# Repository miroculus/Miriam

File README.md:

Miriam
========

**🆕📻⚠️ IMPORTANT: A more updated repository which fixes several critical bugs is at https://github.com/strawlab/Miriam .**

Copyright Miroculus Inc.2016
Based on original work from Arduino (Sweden)

This documentation describes Open Hardware and is licensed under the CERN OHL v. 1.2.

Licensed under CERN OHL v.1.2

You may redistribute and modify this documentation under the terms of the [CERN OHL v.1.2.](http://ohwr.org/cernohl). This documentation is distributed WITHOUT ANY EXPRESS OR IMPLIED WARRANTY, INCLUDING OF MERCHANTABILITY, SATISFACTORY QUALITY AND FITNESS FOR A PARTICULAR PURPOSE. Please see the CERN OHL v.1.2 for applicable conditions

## Introduction

Miriam is an open-source instrument for isothermal amplification reactions. The assays Miriam was designed to execute are based on LAMP and Elisa protocols. Miriam is controlled with [Arduino](http://www.arduino.cc/) Mega and the production costs per instrument are blow 200USD.

The detection optics have been designed for [calcein dye](http://loopamp.eiken.co.jp/e/products/fluore/index.html). The selected LED is an angle SMD led with peak wavelength 461nm. The photodiode is an RGB photodiode most sensitive to green light. The optics also include an emission filter utilized in theatrical lighting.  The development and selection of components is further described in a [Master's thesis](http://lutpub.lut.fi/handle/10024/159386) done from miriam. 

In the performance testing of Miriam, the detection limit for DNA using LAMP as amplification platform has been 2amol in 10ul of sample (figure 1).

**Figure 1.** LAMP reaction with 2amol DNA input, fluorescence measured every 2 minutes (y, Normalized signal and x, cycle (2 min).

For more information, you can contact us by completing the form [here](https://miroculus.com/#contact). You can also follow Miroculus on [twitter](https://twitter.com/miroculus) or like us on [facebook](https://www.facebook.com/miroculus).

To report a *bug* in the software or to request *a simple enhancement* go to the [issues](http://github.com/miroculus/Miriam/issues) section

If you're interested in modifying or extending the Miriam platform, we strongly suggest you to send us an email discussing your ideas. That way you can coordinate with our team and others, giving your work a higher chance of being integrated into the official release.

## Design

The optics of Miriam are designed to support calcein dye. Calcein emission and excitation spectra are represented in Figure 2.

**Figure 2.** Calcein normalized emission and excitation spectra.

The optical filter for blocking the excitation light has been purchased from a theatrical supply store and has the transmission spectra represented in Figure 3.

**Figure 3.** Emission filter transmission specter.

The middle heating board and the LED and PD arrangements have been designed to support 96-well plates with the following dimensions (figure 4).

**Figure 4.** 96-well plate dimensions supported by Miriam

To control the heating of Miriam there are two heater PCBs. They have been designed so that in the middle is a 10 kohm SMD thermistor and the heat is generated by current flowing through the copper traces. These traces have been designed to be so long and narrow that they create an internal resistance of few ohms. The traces are closer to each other in the edges because heat is measured from the middle and the edges of the PCB boards meet ambient air and they need to produce more heat. (Figure 5.)

**Figure 5.** Heating plates, heat is generated by trace resistance. Right: The middle heater creating the temperature required for amplification (58-68 degrees C). Left: The top heater keeping vapor from condensing to the lid, kept at 80 degrees C. 

The detection of fluorescence is done with 96 LEDs and 96 photodiodes creating LED and photodiode PCBs. The LED peak wavelength is 470 nm and photodiode is a green RGB photodiode. The measured voltage is amplified with an operational amplifier to 0-5 V that is then converted by Arduino’s 8-bit ADC to be a numerical value. (figure 6.)

**Figure 6.** LED (left) and photodiode (right) PCBs.

All of these boards are controlled by a shield that is directly mounted to the Arduino mega board (figure 7). The shield contains three MOSFETs to control LED board and the two heater boards, the required components to read the heat from the thermistors as well as a WIFI chip. The WIFI chip makes it possible for Arduino to be connected to a local WIFI and this way communicate autonomously to a web service.

**Figure 7.** The Arduino shield. The power connector is a 20-pin ATX connector that can be connected to a computer ATX power.

Installation
------------
3D print the printable parts under folder "3D model", sand them to make them align with each other. Assemble the boards as presented in the Figure 8. In the assembly cut with scissors the emission filter to fit between the LED and the sensor PCBs so that it aligns with the bolts.

**Figure 8.** PCB board assembly information.

The screws are attached to the cover and the base with heat durable epoxy. 

Credits
--------
Miriam is an open source project, supported by Miroculus in collaboration with Arduino (Sweden). The team is led by Juho Terrijarvi.

Icon and image designed by Miroculus.

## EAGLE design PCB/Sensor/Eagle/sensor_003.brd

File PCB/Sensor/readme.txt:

The used board is FR4, also assembly was done automatically by the manufacturer

- 1oz copper
- 1.6 mm thick
- Leadfree HAL
- White soldermask
- Black silkscreen

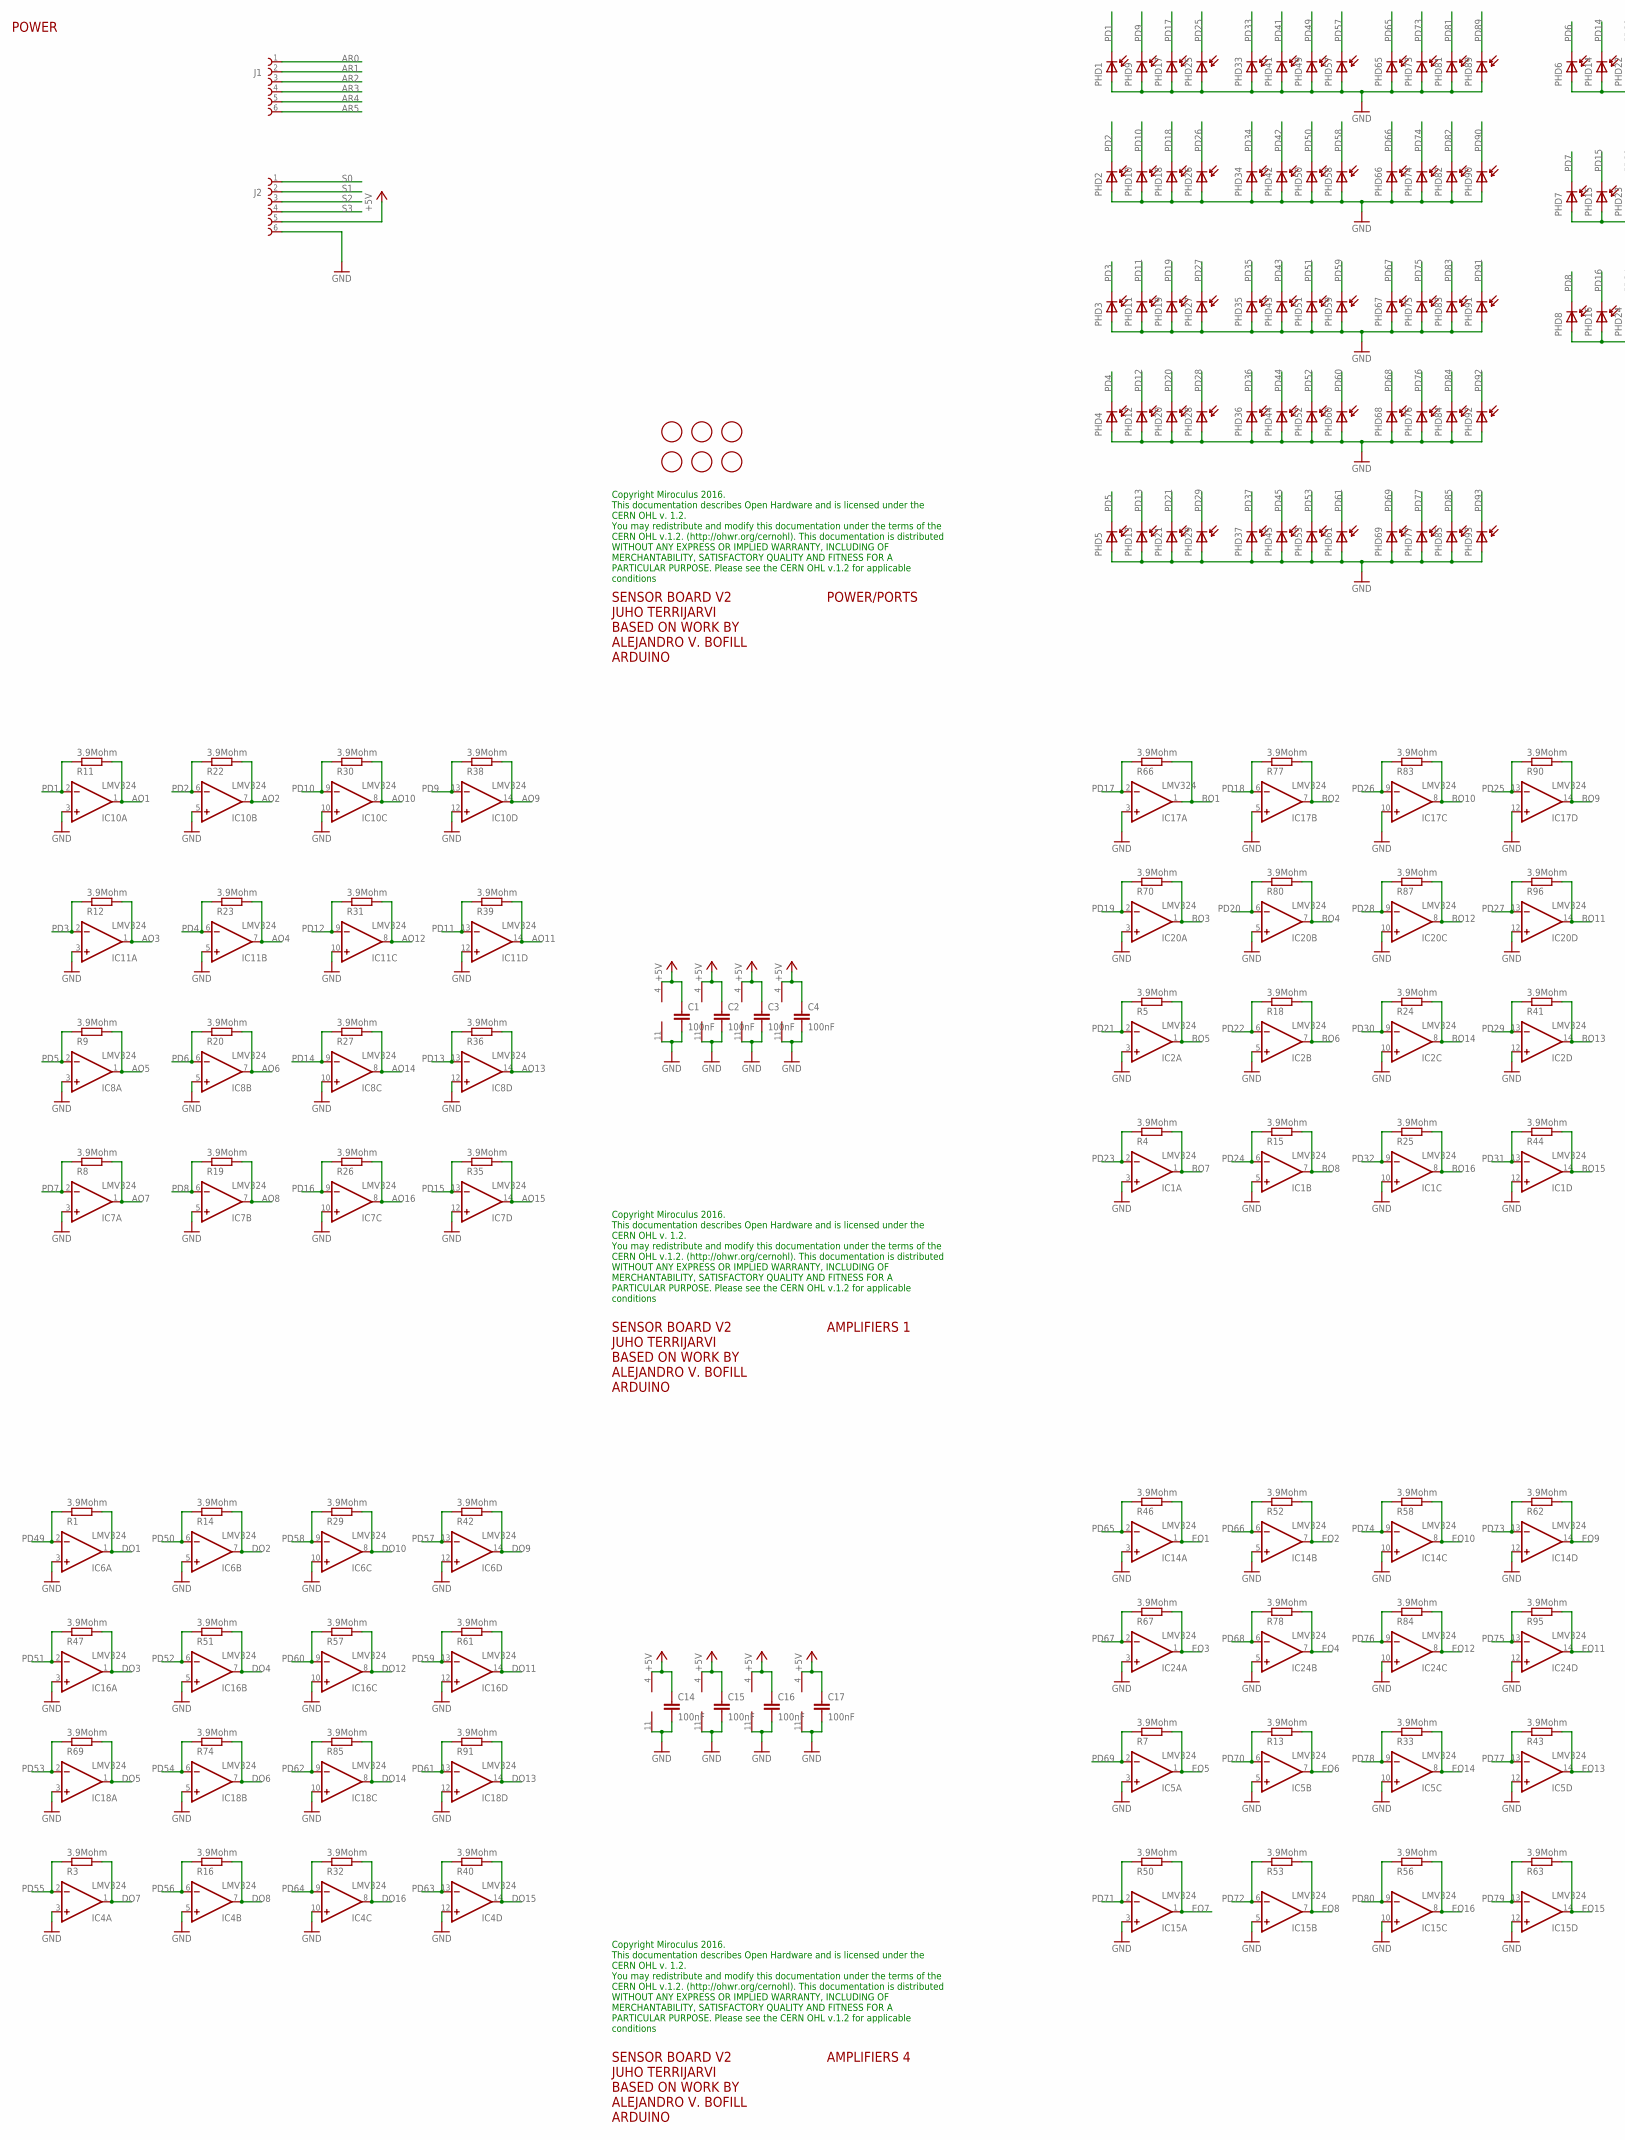
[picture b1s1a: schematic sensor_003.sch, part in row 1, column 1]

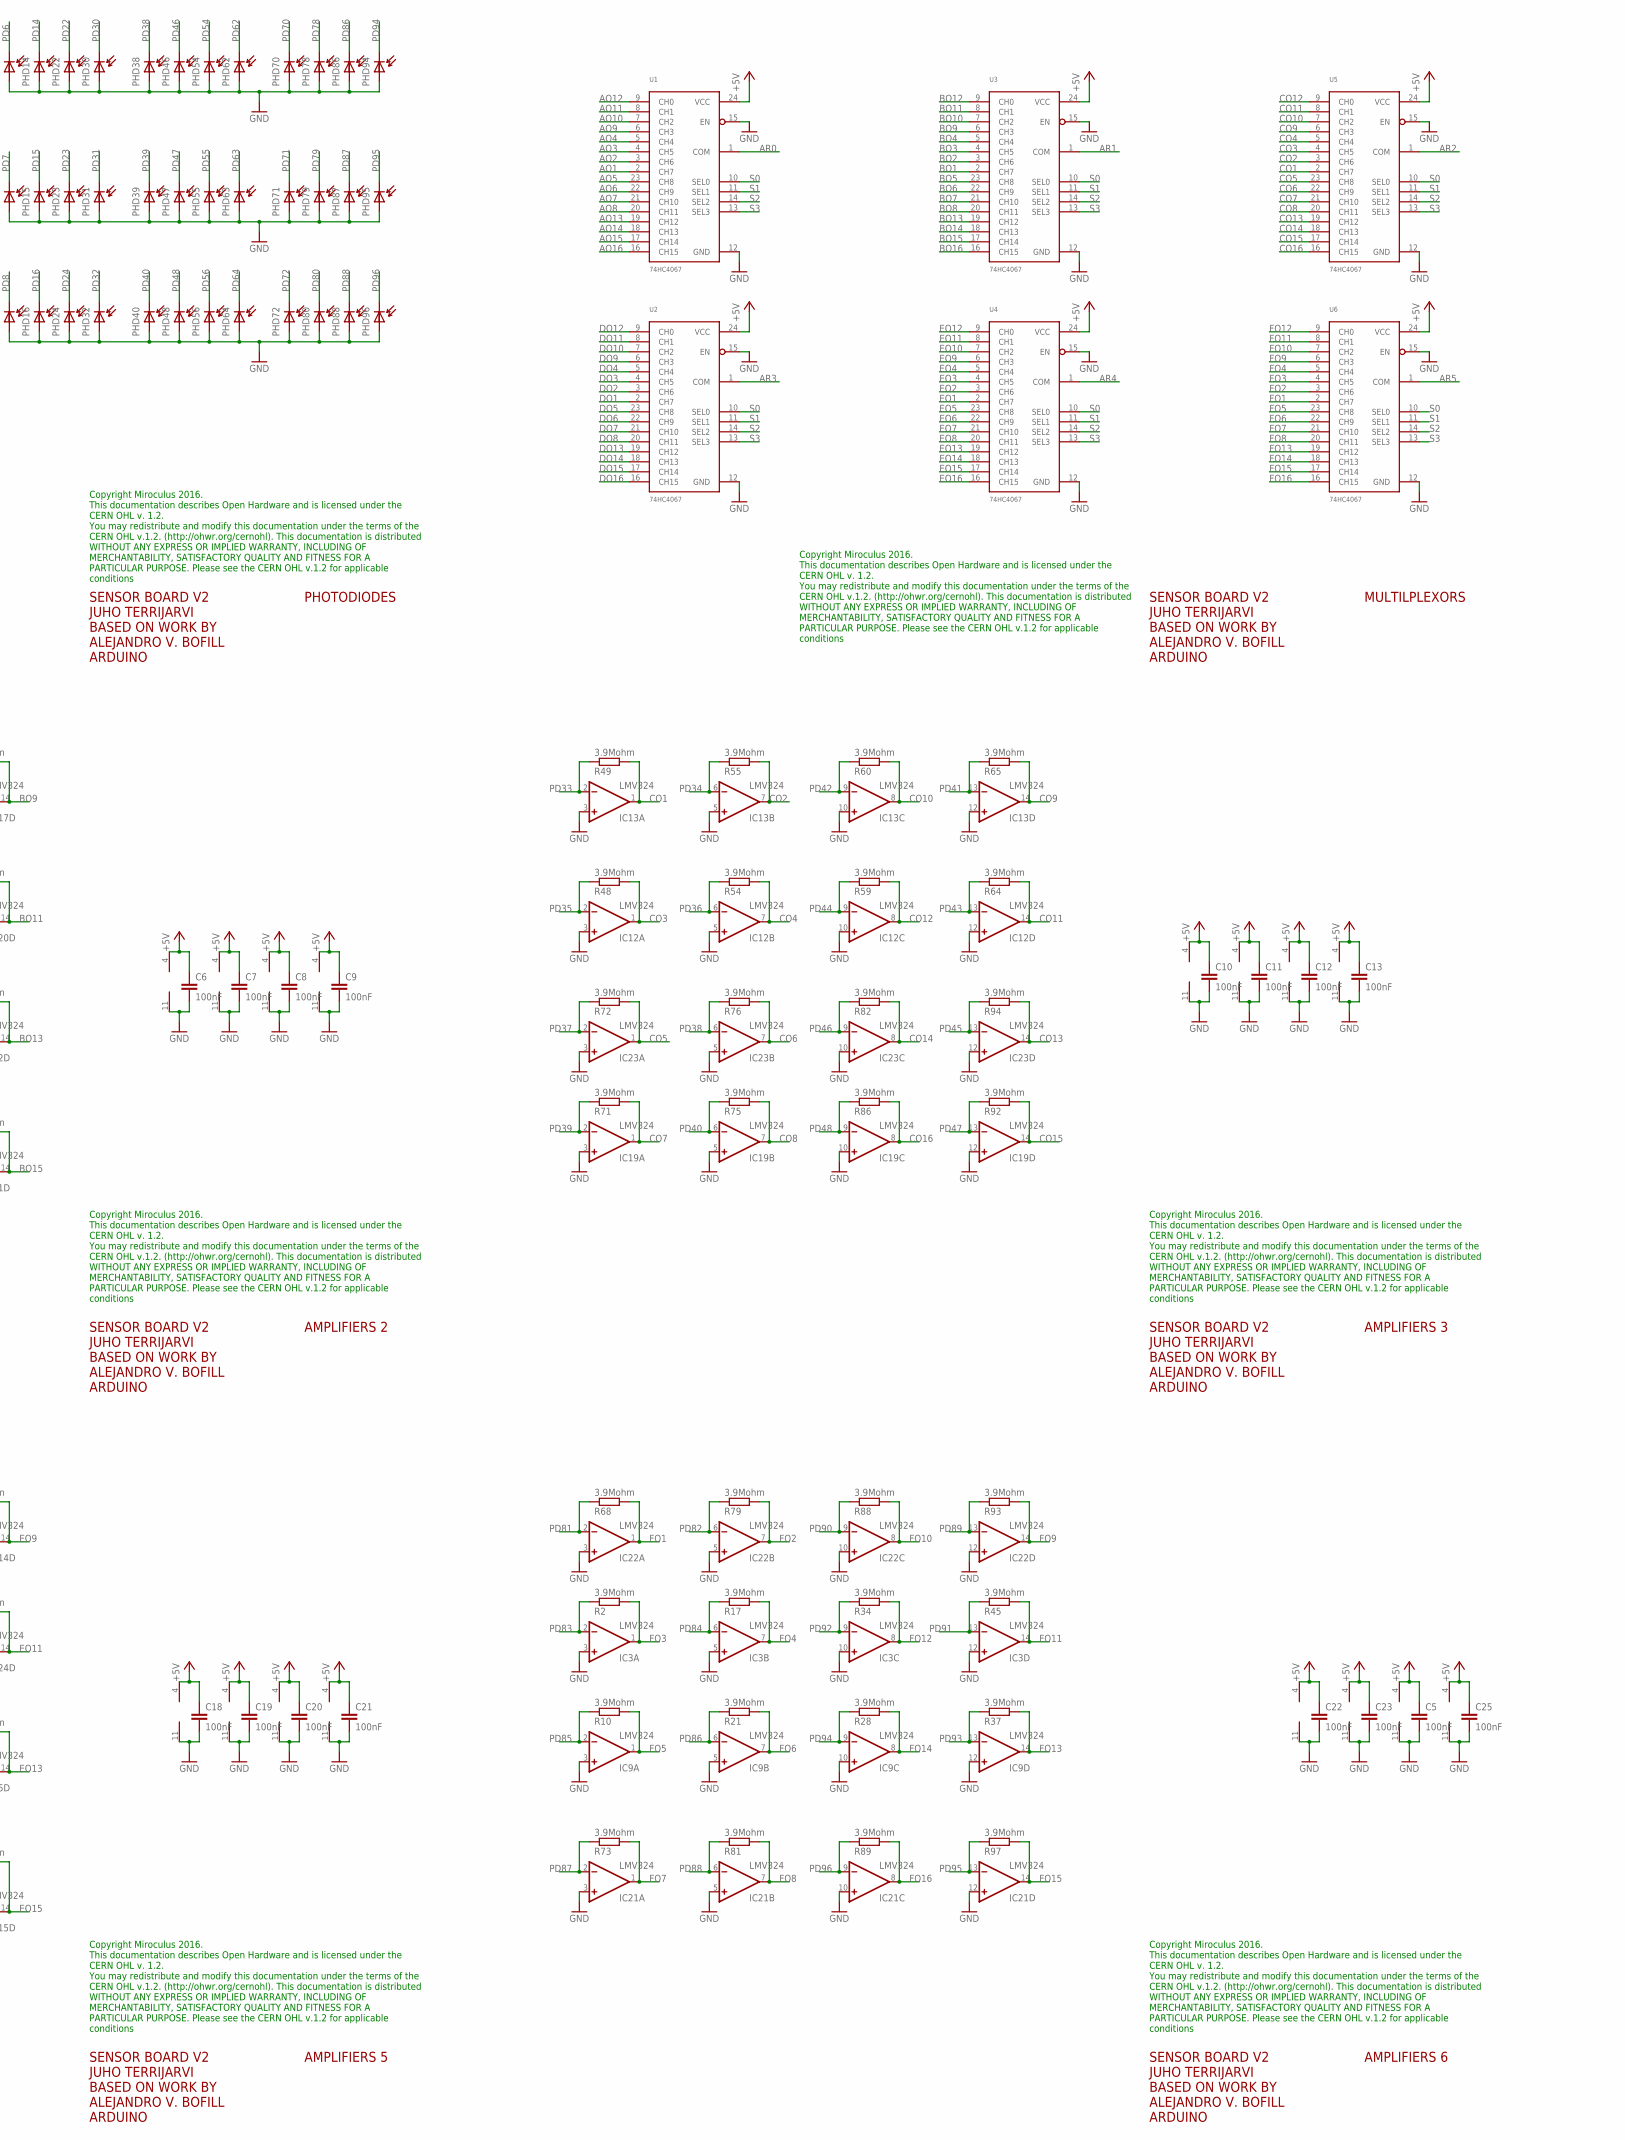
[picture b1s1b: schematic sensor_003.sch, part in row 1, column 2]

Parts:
C1, C2, C3, C4, C5, C6, C7, C8, C9, C10, C11, C12, C13, C14, C15, C16, C17, C18, C19, C20, C21, C22, C23, C25: 100nF; C0603
FD1, FD2, FD3, FD4, FD5, FD6: FIDUCIALMOUNT; FIDUCIA-MOUNT
IC1, IC2, IC3, IC4, IC5, IC6, IC7, IC8, IC9, IC10, IC11, IC12, IC13, IC14, IC15, IC16, IC17, IC18, IC19, IC20, IC21, IC22, IC23, IC24: LMV324; SO14
J1, J2: 68710614522
PHD1, PHD2, PHD3, PHD4, PHD5, PHD6, PHD7, PHD8, PHD9, PHD10, PHD11, PHD12, PHD13, PHD14, PHD15, PHD16, PHD17, PHD18, PHD19, PHD20, PHD21, PHD22, PHD23, PHD24, PHD25, PHD26, PHD27, PHD28, PHD29, PHD30, PHD31, PHD32, PHD33, PHD34, PHD35, PHD36, PHD37, PHD38, PHD39, PHD40, PHD41, PHD42, PHD43, PHD44, PHD45, PHD46, PHD47, PHD48, PHD49, PHD50, PHD51, PHD52, PHD53, PHD54, PHD55, PHD56, PHD57, PHD58, PHD59, PHD60, PHD61, PHD62, PHD63, PHD64, PHD65, PHD66, PHD67, PHD68, PHD69, PHD70, PHD71, PHD72, PHD73, PHD74, PHD75, PHD76, PHD77, PHD78, PHD79, PHD80, PHD81, PHD82, PHD83, PHD84, PHD85, PHD86, PHD87, PHD88, PHD89, PHD90, PHD91, PHD92, PHD93, PHD94, PHD95, PHD96: CLS15-22C/L213G/TR8; PD_0.2
R1, R2, R3, R4, R5, R7, R8, R9, R10, R11, R12, R13, R14, R15, R16, R17, R18, R19, R20, R21, R22, R23, R24, R25, R26, R27, R28, R29, R30, R31, R32, R33, R34, R35, R36, R37, R38, R39, R40, R41, R42, R43, R44, R45, R46, R47, R48, R49, R50, R51, R52, R53, R54, R55, R56, R57, R58, R59, R60, R61, R62, R63, R64, R65, R66, R67, R68, R69, R70, R71, R72, R73, R74, R75, R76, R77, R78, R79, R80, R81, R82, R83, R84, R85, R86, R87, R88, R89, R90, R91, R92, R93, R94, R95, R96, R97: 3.9Mohm; R0603
U1, U2, U3, U4, U5, U6: 74HC4067; SSOP24

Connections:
+5V: C1.1, C2.1, C3.1, C4.1, C5.1, C6.1, C7.1, C8.1, C9.1, C10.1, C11.1, C12.1, C13.1, C14.1, C15.1, C16.1, C17.1, C18.1, C19.1, C20.1, C21.1, C22.1, C23.1, C25.1, IC1.4 (V+), IC2.4 (V+), IC3.4 (V+), IC4.4 (V+), IC5.4 (V+), IC6.4 (V+), IC7.4 (V+), IC8.4 (V+), IC9.4 (V+), IC10.4 (V+), IC11.4 (V+), IC12.4 (V+), IC13.4 (V+), IC14.4 (V+), IC15.4 (V+), IC16.4 (V+), IC17.4 (V+), IC18.4 (V+), IC19.4 (V+), IC20.4 (V+), IC21.4 (V+), IC22.4 (V+), IC23.4 (V+), IC24.4 (V+), J2.5, U1.24 (VCC), U2.24 (VCC), U3.24 (VCC), U4.24 (VCC), U5.24 (VCC), U6.24 (VCC)
AO1: IC10.1 (OUT), R11.2, U1.2 (CH7)
AO2: IC10.7 (OUT), R22.2, U1.3 (CH6)
AO3: IC11.1 (OUT), R12.2, U1.4 (CH5)
AO4: IC11.7 (OUT), R23.2, U1.5 (CH4)
AO5: IC8.1 (OUT), R9.2, U1.23 (CH8)
AO6: IC8.7 (OUT), R20.2, U1.22 (CH9)
AO7: IC7.1 (OUT), R8.2, U1.21 (CH10)
AO8: IC7.7 (OUT), R19.2, U1.20 (CH11)
AO9: IC10.14 (OUT), R38.2, U1.6 (CH3)
AO10: IC10.8 (OUT), R30.2, U1.7 (CH2)
AO11: IC11.14 (OUT), R39.2, U1.8 (CH1)
AO12: IC11.8 (OUT), R31.2, U1.9 (CH0)
AO13: IC8.14 (OUT), R36.2, U1.19 (CH12)
AO14: IC8.8 (OUT), R27.2, U1.18 (CH13)
AO15: IC7.14 (OUT), R35.2, U1.17 (CH14)
AO16: IC7.8 (OUT), R26.2, U1.16 (CH15)
AR0: J1.1, U1.1 (COM)
AR1: J1.2, U3.1 (COM)
AR2: J1.3, U5.1 (COM)
AR3: J1.4, U2.1 (COM)
AR4: J1.5, U4.1 (COM)
AR5: J1.6, U6.1 (COM)
BO1: IC17.1 (OUT), R66.2, U3.2 (CH7)
BO2: IC17.7 (OUT), R77.2, U3.3 (CH6)
BO3: IC20.1 (OUT), R70.2, U3.4 (CH5)
BO4: IC20.7 (OUT), R80.2, U3.5 (CH4)
BO5: IC2.1 (OUT), R5.2, U3.23 (CH8)
BO6: IC2.7 (OUT), R18.2, U3.22 (CH9)
BO7: IC1.1 (OUT), R4.2, U3.21 (CH10)
BO8: IC1.7 (OUT), R15.2, U3.20 (CH11)
BO9: IC17.14 (OUT), R90.2, U3.6 (CH3)
BO10: IC17.8 (OUT), R83.2, U3.7 (CH2)
BO11: IC20.14 (OUT), R96.2, U3.8 (CH1)
BO12: IC20.8 (OUT), R87.2, U3.9 (CH0)
BO13: IC2.14 (OUT), R41.2, U3.19 (CH12)
BO14: IC2.8 (OUT), R24.2, U3.18 (CH13)
BO15: IC1.14 (OUT), R44.2, U3.17 (CH14)
BO16: IC1.8 (OUT), R25.2, U3.16 (CH15)
CO1: IC13.1 (OUT), R49.2, U5.2 (CH7)
CO2: IC13.7 (OUT), R55.2, U5.3 (CH6)
CO3: IC12.1 (OUT), R48.2, U5.4 (CH5)
CO4: IC12.7 (OUT), R54.2, U5.5 (CH4)
CO5: IC23.1 (OUT), R72.2, U5.23 (CH8)
CO6: IC23.7 (OUT), R76.2, U5.22 (CH9)
CO7: IC19.1 (OUT), R71.2, U5.21 (CH10)
CO8: IC19.7 (OUT), R75.2, U5.20 (CH11)
CO9: IC13.14 (OUT), R65.2, U5.6 (CH3)
CO10: IC13.8 (OUT), R60.2, U5.7 (CH2)
CO11: IC12.14 (OUT), R64.2, U5.8 (CH1)
CO12: IC12.8 (OUT), R59.2, U5.9 (CH0)
CO13: IC23.14 (OUT), R94.2, U5.19 (CH12)
CO14: IC23.8 (OUT), R82.2, U5.18 (CH13)
CO15: IC19.14 (OUT), R92.2, U5.17 (CH14)
CO16: IC19.8 (OUT), R86.2, U5.16 (CH15)
DO1: IC6.1 (OUT), R1.2, U2.2 (CH7)
DO2: IC6.7 (OUT), R14.2, U2.3 (CH6)
DO3: IC16.1 (OUT), R47.2, U2.4 (CH5)
DO4: IC16.7 (OUT), R51.2, U2.5 (CH4)
DO5: IC18.1 (OUT), R69.2, U2.23 (CH8)
DO6: IC18.7 (OUT), R74.2, U2.22 (CH9)
DO7: IC4.1 (OUT), R3.2, U2.21 (CH10)
DO8: IC4.7 (OUT), R16.2, U2.20 (CH11)
DO9: IC6.14 (OUT), R42.2, U2.6 (CH3)
DO10: IC6.8 (OUT), R29.2, U2.7 (CH2)
DO11: IC16.14 (OUT), R61.2, U2.8 (CH1)
DO12: IC16.8 (OUT), R57.2, U2.9 (CH0)
DO13: IC18.14 (OUT), R91.2, U2.19 (CH12)
DO14: IC18.8 (OUT), R85.2, U2.18 (CH13)
DO15: IC4.14 (OUT), R40.2, U2.17 (CH14)
DO16: IC4.8 (OUT), R32.2, U2.16 (CH15)
EO1: IC14.1 (OUT), R46.2, U4.2 (CH7)
EO2: IC14.7 (OUT), R52.2, U4.3 (CH6)
EO3: IC24.1 (OUT), R67.2, U4.4 (CH5)
EO4: IC24.7 (OUT), R78.2, U4.5 (CH4)
EO5: IC5.1 (OUT), R7.2, U4.23 (CH8)
EO6: IC5.7 (OUT), R13.2, U4.22 (CH9)
EO7: IC15.1 (OUT), R50.2, U4.21 (CH10)
EO8: IC15.7 (OUT), R53.2, U4.20 (CH11)
EO9: IC14.14 (OUT), R62.2, U4.6 (CH3)
EO10: IC14.8 (OUT), R58.2, U4.7 (CH2)
EO11: IC24.14 (OUT), R95.2, U4.8 (CH1)
EO12: IC24.8 (OUT), R84.2, U4.9 (CH0)
EO13: IC5.14 (OUT), R43.2, U4.19 (CH12)
EO14: IC5.8 (OUT), R33.2, U4.18 (CH13)
EO15: IC15.14 (OUT), R63.2, U4.17 (CH14)
EO16: IC15.8 (OUT), R56.2, U4.16 (CH15)
FO1: IC22.1 (OUT), R68.2, U6.2 (CH7)
FO2: IC22.7 (OUT), R79.2, U6.3 (CH6)
FO3: IC3.1 (OUT), R2.2, U6.4 (CH5)
FO4: IC3.7 (OUT), R17.2, U6.5 (CH4)
FO5: IC9.1 (OUT), R10.2, U6.23 (CH8)
FO6: IC9.7 (OUT), R21.2, U6.22 (CH9)
FO7: IC21.1 (OUT), R73.2, U6.21 (CH10)
FO8: IC21.7 (OUT), R81.2, U6.20 (CH11)
FO9: IC22.14 (OUT), R93.2, U6.6 (CH3)
FO10: IC22.8 (OUT), R88.2, U6.7 (CH2)
FO11: IC3.14 (OUT), R45.2, U6.8 (CH1)
FO12: IC3.8 (OUT), R34.2, U6.9 (CH0)
FO13: IC9.14 (OUT), R37.2, U6.19 (CH12)
FO14: IC9.8 (OUT), R28.2, U6.18 (CH13)
FO15: IC21.14 (OUT), R97.2, U6.17 (CH14)
FO16: IC21.8 (OUT), R89.2, U6.16 (CH15)
GND: C1.2, C2.2, C3.2, C4.2, C5.2, C6.2, C7.2, C8.2, C9.2, C10.2, C11.2, C12.2, C13.2, C14.2, C15.2, C16.2, C17.2, C18.2, C19.2, C20.2, C21.2, C22.2, C23.2, C25.2, IC1.3 (+IN), IC1.5 (+IN), IC1.10 (+IN), IC1.11 (V-), IC1.12 (+IN), IC2.3 (+IN), IC2.5 (+IN), IC2.10 (+IN), IC2.11 (V-), IC2.12 (+IN), IC3.3 (+IN), IC3.5 (+IN), IC3.10 (+IN), IC3.11 (V-), IC3.12 (+IN), IC4.3 (+IN), IC4.5 (+IN), IC4.10 (+IN), IC4.11 (V-), IC4.12 (+IN), IC5.3 (+IN), IC5.5 (+IN), IC5.10 (+IN), IC5.11 (V-), IC5.12 (+IN), IC6.3 (+IN), IC6.5 (+IN), IC6.10 (+IN), IC6.11 (V-), IC6.12 (+IN), IC7.3 (+IN), IC7.5 (+IN), IC7.10 (+IN), IC7.11 (V-), IC7.12 (+IN), IC8.3 (+IN), IC8.5 (+IN), IC8.10 (+IN), IC8.11 (V-), IC8.12 (+IN), IC9.3 (+IN), IC9.5 (+IN), IC9.10 (+IN), IC9.11 (V-), IC9.12 (+IN), IC10.3 (+IN), IC10.5 (+IN), IC10.10 (+IN), IC10.11 (V-), IC10.12 (+IN), IC11.3 (+IN), IC11.5 (+IN), IC11.10 (+IN), IC11.11 (V-), IC11.12 (+IN), IC12.3 (+IN), IC12.5 (+IN), IC12.10 (+IN), IC12.11 (V-), IC12.12 (+IN), IC13.3 (+IN), IC13.5 (+IN), IC13.10 (+IN), IC13.11 (V-), IC13.12 (+IN), IC14.3 (+IN), IC14.5 (+IN), IC14.10 (+IN), IC14.11 (V-), IC14.12 (+IN), IC15.3 (+IN), IC15.5 (+IN), IC15.10 (+IN), IC15.11 (V-), IC15.12 (+IN), IC16.3 (+IN), IC16.5 (+IN), IC16.10 (+IN), IC16.11 (V-), IC16.12 (+IN), IC17.3 (+IN), IC17.5 (+IN), IC17.10 (+IN), IC17.11 (V-), IC17.12 (+IN), IC18.3 (+IN), IC18.5 (+IN), IC18.10 (+IN), IC18.11 (V-), IC18.12 (+IN), IC19.3 (+IN), IC19.5 (+IN), IC19.10 (+IN), IC19.11 (V-), IC19.12 (+IN), IC20.3 (+IN), IC20.5 (+IN), IC20.10 (+IN), IC20.11 (V-), IC20.12 (+IN), IC21.3 (+IN), IC21.5 (+IN), IC21.10 (+IN), IC21.11 (V-), IC21.12 (+IN), IC22.3 (+IN), IC22.5 (+IN), IC22.10 (+IN), IC22.11 (V-), IC22.12 (+IN), IC23.3 (+IN), IC23.5 (+IN), IC23.10 (+IN), IC23.11 (V-), IC23.12 (+IN), IC24.3 (+IN), IC24.5 (+IN), IC24.10 (+IN), IC24.11 (V-), IC24.12 (+IN), J2.6, PHD1.1, PHD1.2 (1), PHD2.1, PHD2.2 (1), PHD3.1, PHD3.2 (1), PHD4.1, PHD4.2 (1), PHD5.1, PHD5.2 (1), PHD6.1, PHD6.2 (1), PHD7.1, PHD7.2 (1), PHD8.1, PHD8.2 (1), PHD9.1, PHD9.2 (1), PHD10.1, PHD10.2 (1), PHD11.1, PHD11.2 (1), PHD12.1, PHD12.2 (1), PHD13.1, PHD13.2 (1), PHD14.1, PHD14.2 (1), PHD15.1, PHD15.2 (1), PHD16.1, PHD16.2 (1), PHD17.1, PHD17.2 (1), PHD18.1, PHD18.2 (1), PHD19.1, PHD19.2 (1), PHD20.1, PHD20.2 (1), PHD21.1, PHD21.2 (1), PHD22.1, PHD22.2 (1), PHD23.1, PHD23.2 (1), PHD24.1, PHD24.2 (1), PHD25.1, PHD25.2 (1), PHD26.1, PHD26.2 (1), PHD27.1, PHD27.2 (1), PHD28.1, PHD28.2 (1), PHD29.1, PHD29.2 (1), PHD30.1, PHD30.2 (1), PHD31.1, PHD31.2 (1), PHD32.1, PHD32.2 (1), PHD33.1, PHD33.2 (1), PHD34.1, PHD34.2 (1), PHD35.1, PHD35.2 (1), PHD36.1, PHD36.2 (1), PHD37.1, PHD37.2 (1), PHD38.1, PHD38.2 (1), PHD39.1, PHD39.2 (1), PHD40.1, PHD40.2 (1), PHD41.1, PHD41.2 (1), PHD42.1, PHD42.2 (1), PHD43.1, PHD43.2 (1), PHD44.1, PHD44.2 (1), PHD45.1, PHD45.2 (1), PHD46.1, PHD46.2 (1), PHD47.1, PHD47.2 (1), PHD48.1, PHD48.2 (1), PHD49.1, PHD49.2 (1), PHD50.1, PHD50.2 (1), PHD51.1, PHD51.2 (1), PHD52.1, PHD52.2 (1), PHD53.1, PHD53.2 (1), PHD54.1, PHD54.2 (1), PHD55.1, PHD55.2 (1), PHD56.1, PHD56.2 (1), PHD57.1, PHD57.2 (1), PHD58.1, PHD58.2 (1), PHD59.1, PHD59.2 (1), PHD60.1, PHD60.2 (1)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
PD1: IC10.2 (-IN), PHD1.3 (2), PHD1.4 (2), R11.1
PD2: IC10.6 (-IN), PHD2.3 (2), PHD2.4 (2), R22.1
PD3: IC11.2 (-IN), PHD3.3 (2), PHD3.4 (2), R12.1
PD4: IC11.6 (-IN), PHD4.3 (2), PHD4.4 (2), R23.1
PD5: IC8.2 (-IN), PHD5.3 (2), PHD5.4 (2), R9.1
PD6: IC8.6 (-IN), PHD6.3 (2), PHD6.4 (2), R20.1
PD7: IC7.2 (-IN), PHD7.3 (2), PHD7.4 (2), R8.1
PD8: IC7.6 (-IN), PHD8.3 (2), PHD8.4 (2), R19.1
PD9: IC10.13 (-IN), PHD9.3 (2), PHD9.4 (2), R38.1
PD10: IC10.9 (-IN), PHD10.3 (2), PHD10.4 (2), R30.1
PD11: IC11.13 (-IN), PHD11.3 (2), PHD11.4 (2), R39.1
PD12: IC11.9 (-IN), PHD12.3 (2), PHD12.4 (2), R31.1
PD13: IC8.13 (-IN), PHD13.3 (2), PHD13.4 (2), R36.1
PD14: IC8.9 (-IN), PHD14.3 (2), PHD14.4 (2), R27.1
PD15: IC7.13 (-IN), PHD15.3 (2), PHD15.4 (2), R35.1
PD16: IC7.9 (-IN), PHD16.3 (2), PHD16.4 (2), R26.1
PD17: IC17.2 (-IN), PHD17.3 (2), PHD17.4 (2), R66.1
PD18: IC17.6 (-IN), PHD18.3 (2), PHD18.4 (2), R77.1
PD19: IC20.2 (-IN), PHD19.3 (2), PHD19.4 (2), R70.1
PD20: IC20.6 (-IN), PHD20.3 (2), PHD20.4 (2), R80.1
PD21: IC2.2 (-IN), PHD21.3 (2), PHD21.4 (2), R5.1
PD22: IC2.6 (-IN), PHD22.3 (2), PHD22.4 (2), R18.1
PD23: IC1.2 (-IN), PHD23.3 (2), PHD23.4 (2), R4.1
PD24: IC1.6 (-IN), PHD24.3 (2), PHD24.4 (2), R15.1
PD25: IC17.13 (-IN), PHD25.3 (2), PHD25.4 (2), R90.1
PD26: IC17.9 (-IN), PHD26.3 (2), PHD26.4 (2), R83.1
PD27: IC20.13 (-IN), PHD27.3 (2), PHD27.4 (2), R96.1
PD28: IC20.9 (-IN), PHD28.3 (2), PHD28.4 (2), R87.1
PD29: IC2.13 (-IN), PHD29.3 (2), PHD29.4 (2), R41.1
PD30: IC2.9 (-IN), PHD30.3 (2), PHD30.4 (2), R24.1
PD31: IC1.13 (-IN), PHD31.3 (2), PHD31.4 (2), R44.1
PD32: IC1.9 (-IN), PHD32.3 (2), PHD32.4 (2), R25.1
PD33: IC13.2 (-IN), PHD33.3 (2), PHD33.4 (2), R49.1
PD34: IC13.6 (-IN), PHD34.3 (2), PHD34.4 (2), R55.1
PD35: IC12.2 (-IN), PHD35.3 (2), PHD35.4 (2), R48.1
PD36: IC12.6 (-IN), PHD36.3 (2), PHD36.4 (2), R54.1
PD37: IC23.2 (-IN), PHD37.3 (2), PHD37.4 (2), R72.1
PD38: IC23.6 (-IN), PHD38.3 (2), PHD38.4 (2), R76.1
PD39: IC19.2 (-IN), PHD39.3 (2), PHD39.4 (2), R71.1
PD40: IC19.6 (-IN), PHD40.3 (2), PHD40.4 (2), R75.1
PD41: IC13.13 (-IN), PHD41.3 (2), PHD41.4 (2), R65.1
PD42: IC13.9 (-IN), PHD42.3 (2), PHD42.4 (2), R60.1
PD43: IC12.13 (-IN), PHD43.3 (2), PHD43.4 (2), R64.1
PD44: IC12.9 (-IN), PHD44.3 (2), PHD44.4 (2), R59.1
PD45: IC23.13 (-IN), PHD45.3 (2), PHD45.4 (2), R94.1
PD46: IC23.9 (-IN), PHD46.3 (2), PHD46.4 (2), R82.1
PD47: IC19.13 (-IN), PHD47.3 (2), PHD47.4 (2), R92.1
PD48: IC19.9 (-IN), PHD48.3 (2), PHD48.4 (2), R86.1
PD49: IC6.2 (-IN), PHD49.3 (2), PHD49.4 (2), R1.1
PD50: IC6.6 (-IN), PHD50.3 (2), PHD50.4 (2), R14.1
PD51: IC16.2 (-IN), PHD51.3 (2), PHD51.4 (2), R47.1
PD52: IC16.6 (-IN), PHD52.3 (2), PHD52.4 (2), R51.1
PD53: IC18.2 (-IN), PHD53.3 (2), PHD53.4 (2), R69.1
PD54: IC18.6 (-IN), PHD54.3 (2), PHD54.4 (2), R74.1
PD55: IC4.2 (-IN), PHD55.3 (2), PHD55.4 (2), R3.1
PD56: IC4.6 (-IN), PHD56.3 (2), PHD56.4 (2), R16.1
PD57: IC6.13 (-IN), PHD57.3 (2), PHD57.4 (2), R42.1
PD58: IC6.9 (-IN), PHD58.3 (2), PHD58.4 (2), R29.1
PD59: IC16.13 (-IN), PHD59.3 (2), PHD59.4 (2), R61.1
PD60: IC16.9 (-IN), PHD60.3 (2), PHD60.4 (2), R57.1
PD61: IC18.13 (-IN), PHD61.3 (2), PHD61.4 (2), R91.1
PD62: IC18.9 (-IN), PHD62.3 (2), PHD62.4 (2), R85.1
PD63: IC4.13 (-IN), PHD63.3 (2), PHD63.4 (2), R40.1
PD64: IC4.9 (-IN), PHD64.3 (2), PHD64.4 (2), R32.1
PD65: IC14.2 (-IN), PHD65.3 (2), PHD65.4 (2), R46.1
PD66: IC14.6 (-IN), PHD66.3 (2), PHD66.4 (2), R52.1
PD67: IC24.2 (-IN), PHD67.3 (2), PHD67.4 (2), R67.1
PD68: IC24.6 (-IN), PHD68.3 (2), PHD68.4 (2), R78.1
PD69: IC5.2 (-IN), PHD69.3 (2), PHD69.4 (2), R7.1
PD70: IC5.6 (-IN), PHD70.3 (2), PHD70.4 (2), R13.1
PD71: IC15.2 (-IN), PHD71.3 (2), PHD71.4 (2), R50.1
PD72: IC15.6 (-IN), PHD72.3 (2), PHD72.4 (2), R53.1
PD73: IC14.13 (-IN), PHD73.3 (2), PHD73.4 (2), R62.1
PD74: IC14.9 (-IN), PHD74.3 (2), PHD74.4 (2), R58.1
PD75: IC24.13 (-IN), PHD75.3 (2), PHD75.4 (2), R95.1
PD76: IC24.9 (-IN), PHD76.3 (2), PHD76.4 (2), R84.1
PD77: IC5.13 (-IN), PHD77.3 (2), PHD77.4 (2), R43.1
PD78: IC5.9 (-IN), PHD78.3 (2), PHD78.4 (2), R33.1
PD79: IC15.13 (-IN), PHD79.3 (2), PHD79.4 (2), R63.1
PD80: IC15.9 (-IN), PHD80.3 (2), PHD80.4 (2), R56.1
PD81: IC22.2 (-IN), PHD81.3 (2), PHD81.4 (2), R68.1
PD82: IC22.6 (-IN), PHD82.3 (2), PHD82.4 (2), R79.1
PD83: IC3.2 (-IN), PHD83.3 (2), PHD83.4 (2), R2.1
PD84: IC3.6 (-IN), PHD84.3 (2), PHD84.4 (2), R17.1
PD85: IC9.2 (-IN), PHD85.3 (2), PHD85.4 (2), R10.1
PD86: IC9.6 (-IN), PHD86.3 (2), PHD86.4 (2), R21.1
PD87: IC21.2 (-IN), PHD87.3 (2), PHD87.4 (2), R73.1
PD88: IC21.6 (-IN), PHD88.3 (2), PHD88.4 (2), R81.1
PD89: IC22.13 (-IN), PHD89.3 (2), PHD89.4 (2), R93.1
PD90: IC22.9 (-IN), PHD90.3 (2), PHD90.4 (2), R88.1
PD91: IC3.13 (-IN), PHD91.3 (2), PHD91.4 (2), R45.1
PD92: IC3.9 (-IN), PHD92.3 (2), PHD92.4 (2), R34.1
PD93: IC9.13 (-IN), PHD93.3 (2), PHD93.4 (2), R37.1
PD94: IC9.9 (-IN), PHD94.3 (2), PHD94.4 (2), R28.1
PD95: IC21.13 (-IN), PHD95.3 (2), PHD95.4 (2), R97.1
PD96: IC21.9 (-IN), PHD96.3 (2), PHD96.4 (2), R89.1
S0: J2.1, U1.10 (SEL0), U2.10 (SEL0), U3.10 (SEL0), U4.10 (SEL0), U5.10 (SEL0), U6.10 (SEL0)
S1: J2.2, U1.11 (SEL1), U2.11 (SEL1), U3.11 (SEL1), U4.11 (SEL1), U5.11 (SEL1), U6.11 (SEL1)
S2: J2.3, U1.14 (SEL2), U2.14 (SEL2), U3.14 (SEL2), U4.14 (SEL2), U5.14 (SEL2), U6.14 (SEL2)
S3: J2.4, U1.13 (SEL3), U2.13 (SEL3), U3.13 (SEL3), U4.13 (SEL3), U5.13 (SEL3), U6.13 (SEL3)

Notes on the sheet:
SENSOR BOARD V2 JUHO TERRIJARVI BASED ON WORK BY ALEJANDRO V. BOFILL ARDUINO
POWER
POWER/PORTS
PHOTODIODES
AMPLIFIERS 1
AMPLIFIERS 2
AMPLIFIERS 3
AMPLIFIERS 4
AMPLIFIERS 5
AMPLIFIERS 6
MULTILPLEXORS
Copyright Miroculus 2016. This documentation describes Open Hardware and is licensed under the CERN OHL v. 1.2. You may redistribute and modify this documentation under the terms of the CERN OHL v.1.2. (http://ohwr.org/cernohl). This documentation is distributed WITHOUT ANY EXPRESS OR IMPLIED WARRA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

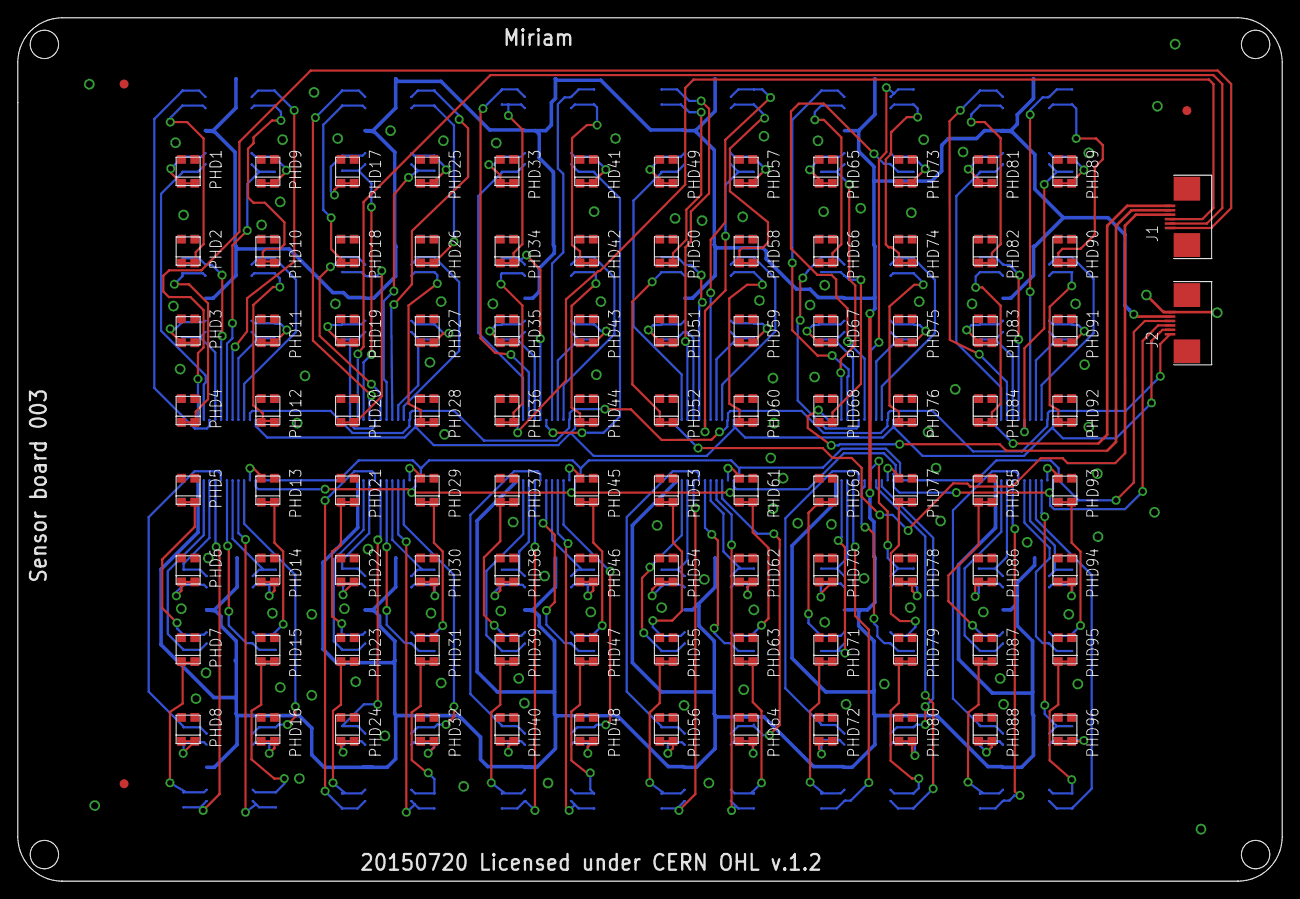
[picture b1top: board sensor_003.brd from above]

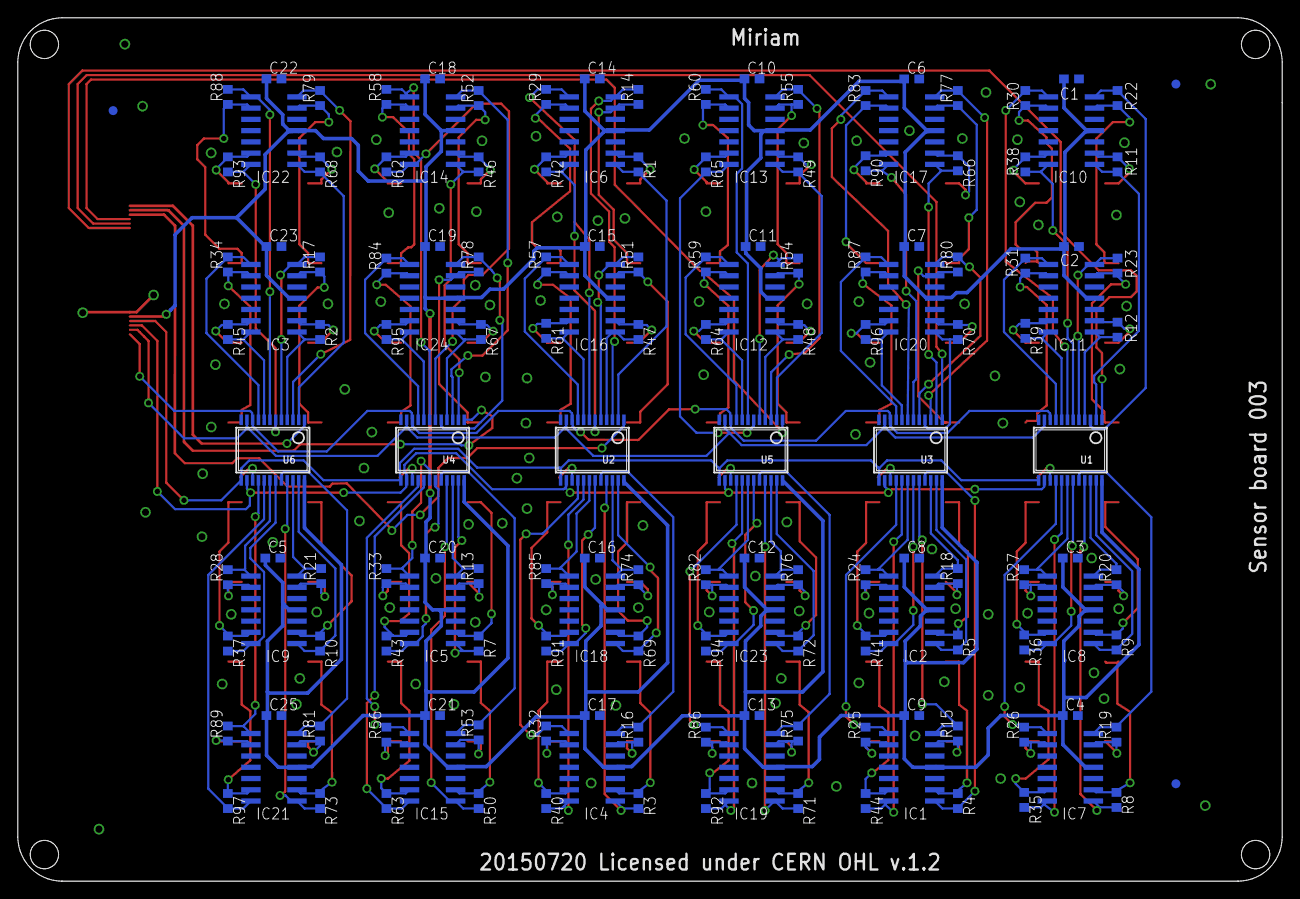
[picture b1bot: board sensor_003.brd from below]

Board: 2 copper layers, 142.8 x 97.5 mm, 254 parts (153 on the bottom side), 204 nets.

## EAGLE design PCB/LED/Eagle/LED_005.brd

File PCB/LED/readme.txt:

The used board is FR4, also assembly was done automatically by the manufacturer

- 1oz copper
- 1.6 mm thick
- Leadfree HAL
- Black soldermask
- White silkscreen

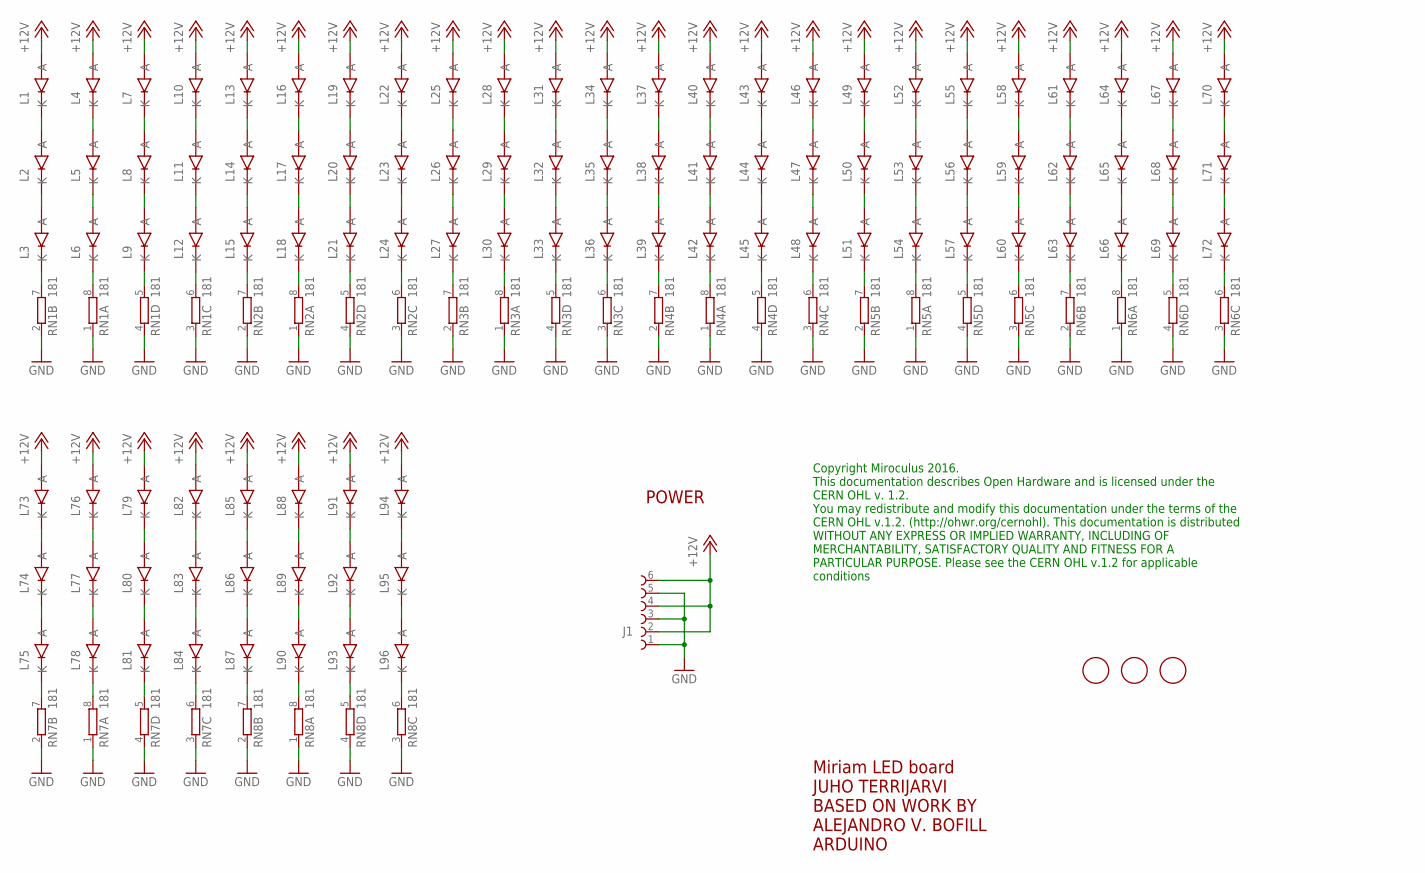
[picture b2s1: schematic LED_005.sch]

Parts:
FD1, FD2, FD3: FIDUCIALMOUNT; FIDUCIA-MOUNT
J1: 68710614522
L1, L2, L3, L4, L5, L6, L7, L8, L9, L10, L11, L12, L13, L14, L15, L16, L17, L18, L19, L20, L21, L22, L23, L24, L25, L26, L27, L28, L29, L30, L31, L32, L33, L34, L35, L36, L37, L38, L39, L40, L41, L42, L43, L44, L45, L46, L47, L48, L49, L50, L51, L52, L53, L54, L55, L56, L57, L58, L59, L60, L61, L62, L63, L64, L65, L66, L67, L68, L69, L70, L71, L72, L73, L74, L75, L76, L77, L78, L79, L80, L81, L82, L83, L84, L85, L86, L87, L88, L89, L90, L91, L92, L93, L94, L95, L96: KA-2810AQBS-G; LED_0.2
RN1, RN2, RN3, RN4, RN5, RN6, RN7, RN8: 181; CAY16

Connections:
+12V: J1.2, J1.4, J1.6, L1.2 (A), L4.2 (A), L7.2 (A), L10.2 (A), L13.2 (A), L16.2 (A), L19.2 (A), L22.2 (A), L25.2 (A), L28.2 (A), L31.2 (A), L34.2 (A), L37.2 (A), L40.2 (A), L43.2 (A), L46.2 (A), L49.2 (A), L52.2 (A), L55.2 (A), L58.2 (A), L61.2 (A), L64.2 (A), L67.2 (A), L70.2 (A), L73.2 (A), L76.2 (A), L79.2 (A), L82.2 (A), L85.2 (A), L88.2 (A), L91.2 (A), L94.2 (A)
GND: J1.1, J1.3, J1.5, RN1.1, RN1.2 (1), RN1.3 (1), RN1.4 (1), RN2.1, RN2.2 (1), RN2.3 (1), RN2.4 (1), RN3.1, RN3.2 (1), RN3.3 (1), RN3.4 (1), RN4.1, RN4.2 (1), RN4.3 (1), RN4.4 (1), RN5.1, RN5.2 (1), RN5.3 (1), RN5.4 (1), RN6.1, RN6.2 (1), RN6.3 (1), RN6.4 (1), RN7.1, RN7.2 (1), RN7.3 (1), RN7.4 (1), RN8.1, RN8.2 (1), RN8.3 (1), RN8.4 (1)
unnamed: L1.1 (K), L2.2 (A)
unnamed: L2.1 (K), L3.2 (A)
unnamed: L3.1 (K), RN1.7 (2)
unnamed: L4.1 (K), L5.2 (A)
unnamed: L5.1 (K), L6.2 (A)
unnamed: L6.1 (K), RN1.8 (2)
unnamed: L7.1 (K), L8.2 (A)
unnamed: L8.1 (K), L9.2 (A)
unnamed: L9.1 (K), RN1.5 (2)
unnamed: L10.1 (K), L11.2 (A)
unnamed: L11.1 (K), L12.2 (A)
unnamed: L12.1 (K), RN1.6 (2)
unnamed: L13.1 (K), L14.2 (A)
unnamed: L14.1 (K), L15.2 (A)
unnamed: L16.1 (K), L17.2 (A)
unnamed: L17.1 (K), L18.2 (A)
unnamed: L19.1 (K), L20.2 (A)
unnamed: L20.1 (K), L21.2 (A)
unnamed: L22.1 (K), L23.2 (A)
unnamed: L23.1 (K), L24.2 (A)
unnamed: L15.1 (K), RN2.7 (2)
unnamed: L18.1 (K), RN2.8 (2)
unnamed: L21.1 (K), RN2.5 (2)
unnamed: L24.1 (K), RN2.6 (2)
unnamed: L25.1 (K), L26.2 (A)
unnamed: L26.1 (K), L27.2 (A)
unnamed: L28.1 (K), L29.2 (A)
unnamed: L29.1 (K), L30.2 (A)
unnamed: L31.1 (K), L32.2 (A)
unnamed: L32.1 (K), L33.2 (A)
unnamed: L34.1 (K), L35.2 (A)
unnamed: L35.1 (K), L36.2 (A)
unnamed: L27.1 (K), RN3.7 (2)
unnamed: L30.1 (K), RN3.8 (2)
unnamed: L33.1 (K), RN3.5 (2)
unnamed: L36.1 (K), RN3.6 (2)
unnamed: L37.1 (K), L38.2 (A)
unnamed: L38.1 (K), L39.2 (A)
unnamed: L40.1 (K), L41.2 (A)
unnamed: L41.1 (K), L42.2 (A)
unnamed: L43.1 (K), L44.2 (A)
unnamed: L44.1 (K), L45.2 (A)
unnamed: L46.1 (K), L47.2 (A)
unnamed: L47.1 (K), L48.2 (A)
unnamed: L39.1 (K), RN4.7 (2)
unnamed: L42.1 (K), RN4.8 (2)
unnamed: L45.1 (K), RN4.5 (2)
unnamed: L48.1 (K), RN4.6 (2)
unnamed: L49.1 (K), L50.2 (A)
unnamed: L50.1 (K), L51.2 (A)
unnamed: L52.1 (K), L53.2 (A)
unnamed: L53.1 (K), L54.2 (A)
unnamed: L55.1 (K), L56.2 (A)
unnamed: L56.1 (K), L57.2 (A)
unnamed: L58.1 (K), L59.2 (A)
unnamed: L59.1 (K), L60.2 (A)
unnamed: L51.1 (K), RN5.7 (2)
unnamed: L54.1 (K), RN5.8 (2)
unnamed: L57.1 (K), RN5.5 (2)
unnamed: L60.1 (K), RN5.6 (2)
unnamed: L61.1 (K), L62.2 (A)
unnamed: L62.1 (K), L63.2 (A)
unnamed: L64.1 (K), L65.2 (A)
unnamed: L65.1 (K), L66.2 (A)
unnamed: L67.1 (K), L68.2 (A)
unnamed: L68.1 (K), L69.2 (A)
unnamed: L70.1 (K), L71.2 (A)
unnamed: L71.1 (K), L72.2 (A)
unnamed: L63.1 (K), RN6.7 (2)
unnamed: L66.1 (K), RN6.8 (2)
unnamed: L69.1 (K), RN6.5 (2)
unnamed: L72.1 (K), RN6.6 (2)
unnamed: L73.1 (K), L74.2 (A)
unnamed: L74.1 (K), L75.2 (A)
unnamed: L76.1 (K), L77.2 (A)
unnamed: L77.1 (K), L78.2 (A)
unnamed: L79.1 (K), L80.2 (A)
unnamed: L80.1 (K), L81.2 (A)
unnamed: L82.1 (K), L83.2 (A)
unnamed: L83.1 (K), L84.2 (A)
unnamed: L96.1 (K), RN8.6 (2)
unnamed: L93.1 (K), RN8.5 (2)
unnamed: L90.1 (K), RN8.8 (2)
unnamed: L87.1 (K), RN8.7 (2)
unnamed: L85.1 (K), L86.2 (A)
unnamed: L86.1 (K), L87.2 (A)
unnamed: L88.1 (K), L89.2 (A)
unnamed: L89.1 (K), L90.2 (A)
unnamed: L91.1 (K), L92.2 (A)
unnamed: L92.1 (K), L93.2 (A)
unnamed: L94.1 (K), L95.2 (A)
unnamed: L95.1 (K), L96.2 (A)
unnamed: L84.1 (K), RN7.6 (2)
unnamed: L81.1 (K), RN7.5 (2)
unnamed: L78.1 (K), RN7.8 (2)
unnamed: L75.1 (K), RN7.7 (2)

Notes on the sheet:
POWER
Miriam LED board JUHO TERRIJARVI BASED ON WORK BY ALEJANDRO V. BOFILL ARDUINO
Copyright Miroculus 2016. This documentation describes Open Hardware and is licensed under the CERN OHL v. 1.2. You may redistribute and modify this documentation under the terms of the CERN OHL v.1.2. (http://ohwr.org/cernohl). This documentation is distributed WITHOUT ANY EXPRESS OR IMPLIED WARRA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

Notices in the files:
PCB/LED/Eagle/LED_005.brd:
20160322 Licensed under CERN OHL v.1.2
PCB/Lower heating board/Eagle/LH_009.brd:
20150911 Licensed under CERN OHL v.1.2
PCB/Sensor/Eagle/sensor_003.brd:
20150720 Licensed under CERN OHL v.1.2
PCB/Upper heating board/Eagle/UH_006.brd:
20150918 Licensed under CERN OHL v.1.2
README.md:
CC BY-SA 3.0
parts and their libraries:
Eagle_FPC_CONNECTOR_AND_FFC_CAB: Copyright: Würth Elektronik
microbuilder: This work is placed in the public domain, and may be freely used for commercial and non-commercial work with the following conditions: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
